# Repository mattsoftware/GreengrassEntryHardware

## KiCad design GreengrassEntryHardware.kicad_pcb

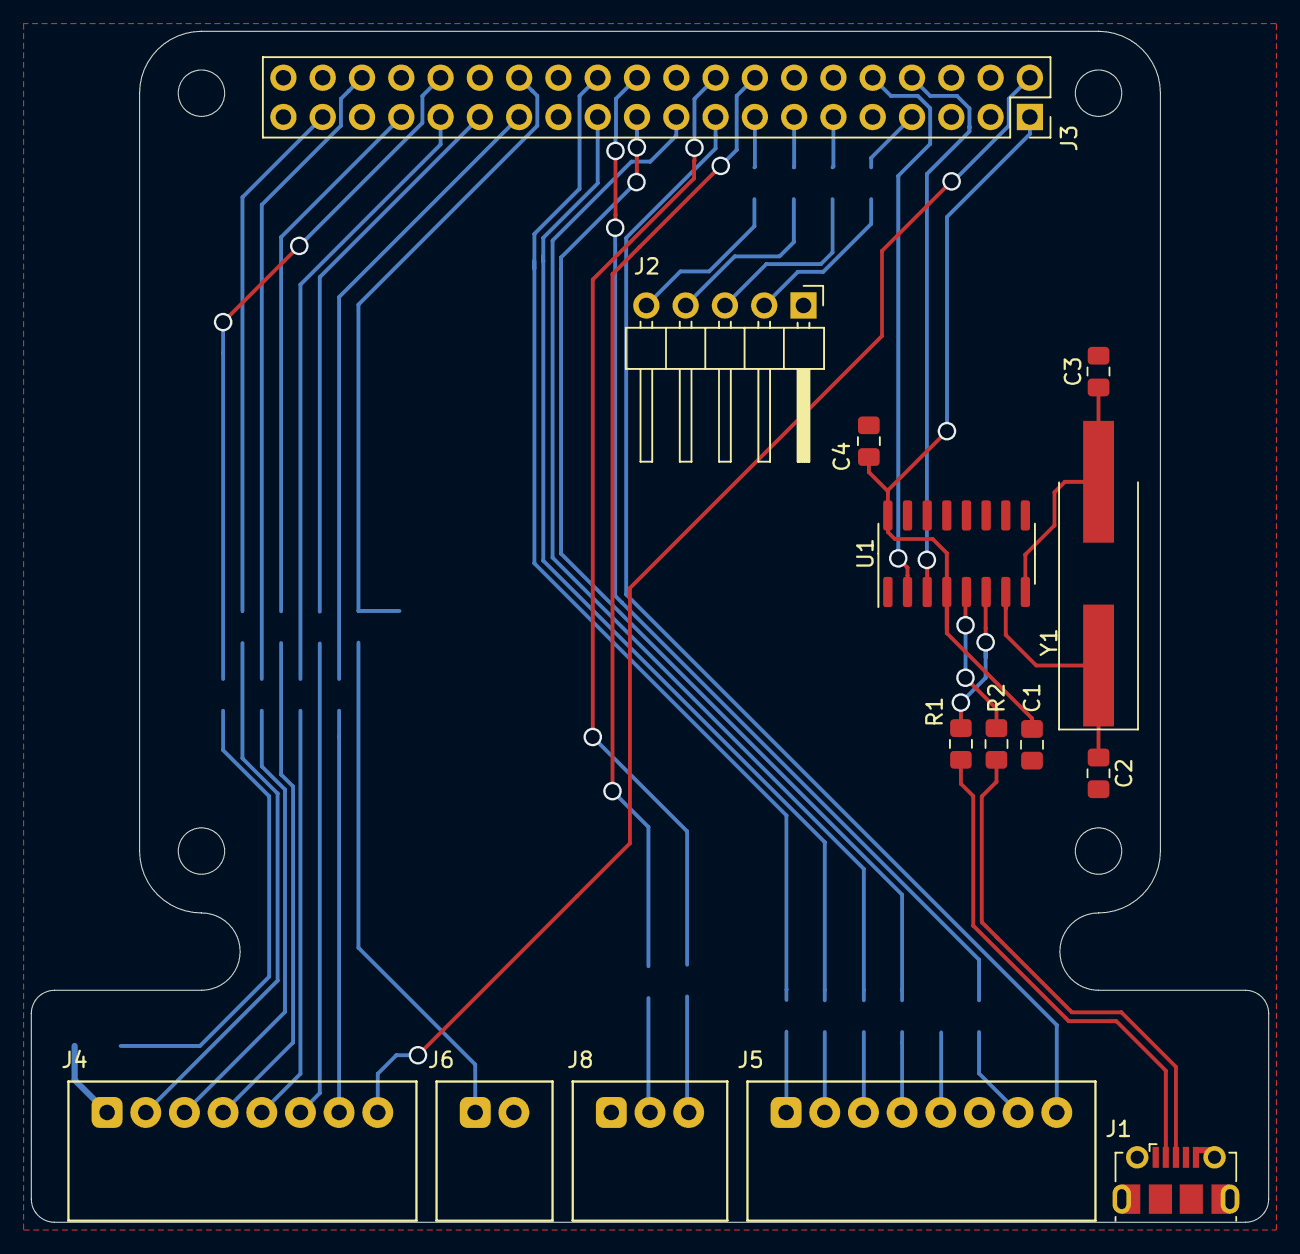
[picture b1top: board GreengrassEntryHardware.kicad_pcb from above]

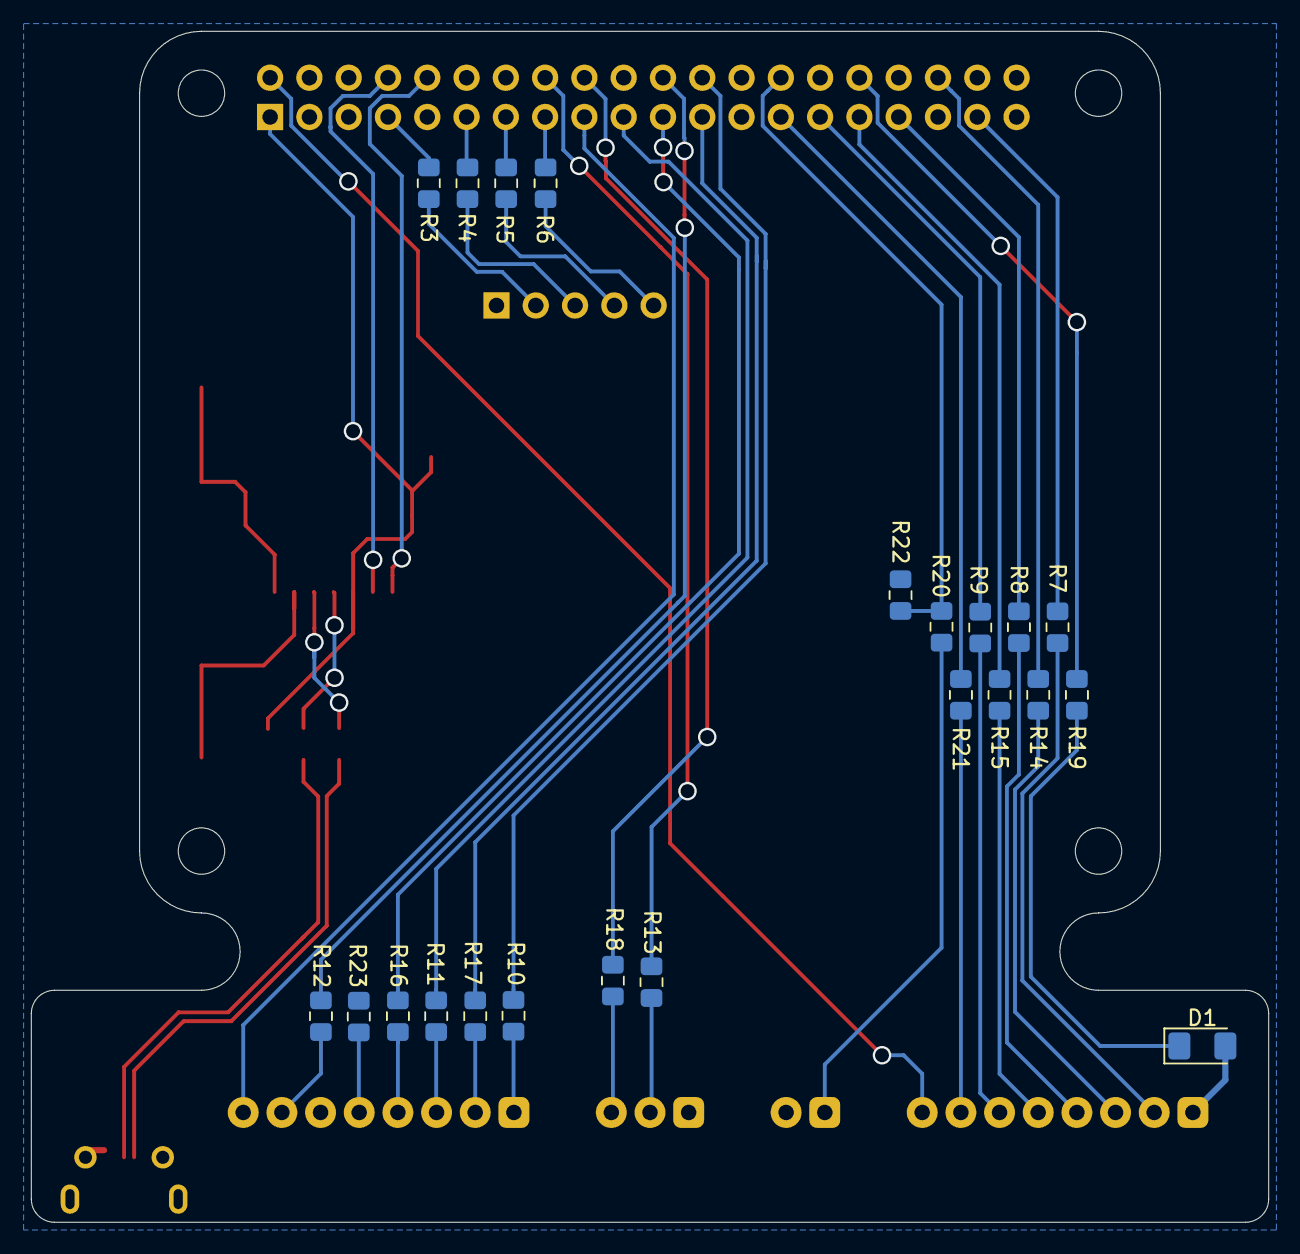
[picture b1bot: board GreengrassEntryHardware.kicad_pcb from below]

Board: 2 copper layers, 80.0 x 77.0 mm, 37 parts (22 on the bottom side), 51 nets.

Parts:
C1, C4: 10n; C_0805_2012Metric_Pad1.15x1.40mm_HandSolder
C2, C3: 22p; C_0805_2012Metric_Pad1.15x1.40mm_HandSolder
D1: LED_ALT; LED_1206_3216Metric_Pad1.42x1.75mm_HandSolder
J1: USB_B_Micro; USB_Micro-B_Molex-105017-0001
J2: GPIOBreakout; PinHeader_1x05_P2.54mm_Horizontal
J3: Raspberry_Pi_2_3; PinSocket_2x20_P2.54mm_Vertical
J4: AutomaticSlidingDoor; Molex-MiniSpox-22057xx5-08-Horizontal
J5: MFRC-522; Molex-MiniSpox-22057xx5-08-Horizontal
J6: DoorEnable; Molex-MiniSpox-22057025-02-Horizontal
J8: FEEDBACK; Molex-MiniSpox-22057025-03-Horizontal
R1, R2, R3, R4, R5, R6, R7, R8, R9, R10, R11, R12, R13, R14, R15, R16, R17, R18, R19, R20, R21, R23: 27; R_0805_2012Metric_Pad1.15x1.40mm_HandSolder
R22: 10k; R_0805_2012Metric_Pad1.15x1.40mm_HandSolder
U1: CH340G; SOIC-16_3.9x9.9mm_P1.27mm
Y1: 12MHZ; Crystal_SMD_HC49-SD_HandSoldering

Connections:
/D+: J1.3, R2.2
/D-: J1.2, R1.2
ACTIVATE: J3.37, R7.2
AUTO: J3.31, R15.2
AUTO_OUT: J3.29, R9.2
CLOSED: J3.27, R21.2
ENABLE: J3.28, R20.2, R22.1
EXIT: J3.36, R14.2
FEEDBACK-BUZZER: J3.16, R13.2
FEEDBACK-LED: J3.18, R18.2
GNDD: C1.2, C2.2, C3.2, C4.2, D1.2, J1.5, J1.6, J2.1, J3.6, J3.9, J3.14, J3.20, J3.25, J3.30, J3.34, J3.39, J4.1, J5.6, J6.2, J8.1, R22.2, U1.1
GPIO4: J3.7, R3.1
GPIO17: J3.11, R4.1
GPIO22: J3.15, R6.1
GPIO27: J3.13, R5.1
unnamed: C1.1, C4.1, J3.1, U1.4, U1.16
unnamed: C2.1, U1.7, Y1.1
unnamed: C3.1, U1.8, Y1.2
unnamed: D1.1, R19.1
unnamed: J2.2, R3.2
unnamed: J2.3, R4.2
unnamed: J2.4, R5.2
unnamed: J2.5, R6.2
unnamed: J3.2, J4.8
unnamed: J3.8, U1.3
unnamed: J3.10, U1.2
unnamed: J3.17, J5.8
unnamed: J3.32, R19.2
unnamed: J4.2, R7.1
unnamed: J4.3, R14.1
unnamed: J4.4, R8.1
unnamed: J4.5, R15.1
unnamed: J4.6, R9.1
unnamed: J4.7, R21.1
unnamed: J5.1, R10.1
unnamed: J5.2, R17.1
unnamed: J5.3, R11.1
unnamed: J5.4, R16.1
unnamed: J5.5, R23.1
unnamed: J5.7, R12.1
unnamed: J6.1, R20.1
unnamed: J8.2, R13.1
unnamed: J8.3, R18.1
unnamed: R1.1, U1.6
unnamed: R2.1, U1.5
OPEN: J3.33, R8.2
RFID-CS: J3.24, R10.2
RFID-MISO: J3.21, R16.2
RFID-MOSI: J3.19, R11.2
RFID-RST: J3.22, R12.2
RFID-SCK: J3.23, R17.2

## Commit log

2019-07-25 Initial schematic for the greengrass entry system
2019-07-25 Small tweak to layout
2019-07-26 WIP: finished usb to uart design
2019-07-26 Added GPIO breakout to pcb
2019-07-28 Tidied up the mfrc pcb layout
2019-07-29 Added the door connector to the pcb
2019-07-29 Saved some molex connectors with 3d models
2019-07-29 Update schematic and pcb to use Molex SPOX connector for the automatic door
2019-07-29 Added a status led
2019-07-29 Make the USB pads bigger
2019-07-29 Some tweaks before changing mfrc connector to molex
2019-07-30 Added molex connector for mfrc and added net labels
2019-07-30 Increase vias size, design rules, back plane, copyright
2019-07-30 Tweak some tracks to maximise groundplane
2019-08-01 Used wrong footprint for LED
2019-08-10 Radical redesign using nets, mini spox, larger board, traces on underside
2019-08-10 Cleanup edge cuts and fill layers, fix some connectors not on back side
2019-08-11 Tidy up pcb and annotate with v1.0
2019-08-11 Push 5v to the relays
2019-08-17 Generated Gerber files
2022-02-27 Files that were modified by forgotted to commit
2022-02-27 Added the RelaySupportBoard WIP

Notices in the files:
GreengrassEntryHardware.kicad_pcb:
License: CC By 4.0
